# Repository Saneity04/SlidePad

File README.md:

# SlidePad
3x3 matrix with 4 Slider potentiometer running QMK

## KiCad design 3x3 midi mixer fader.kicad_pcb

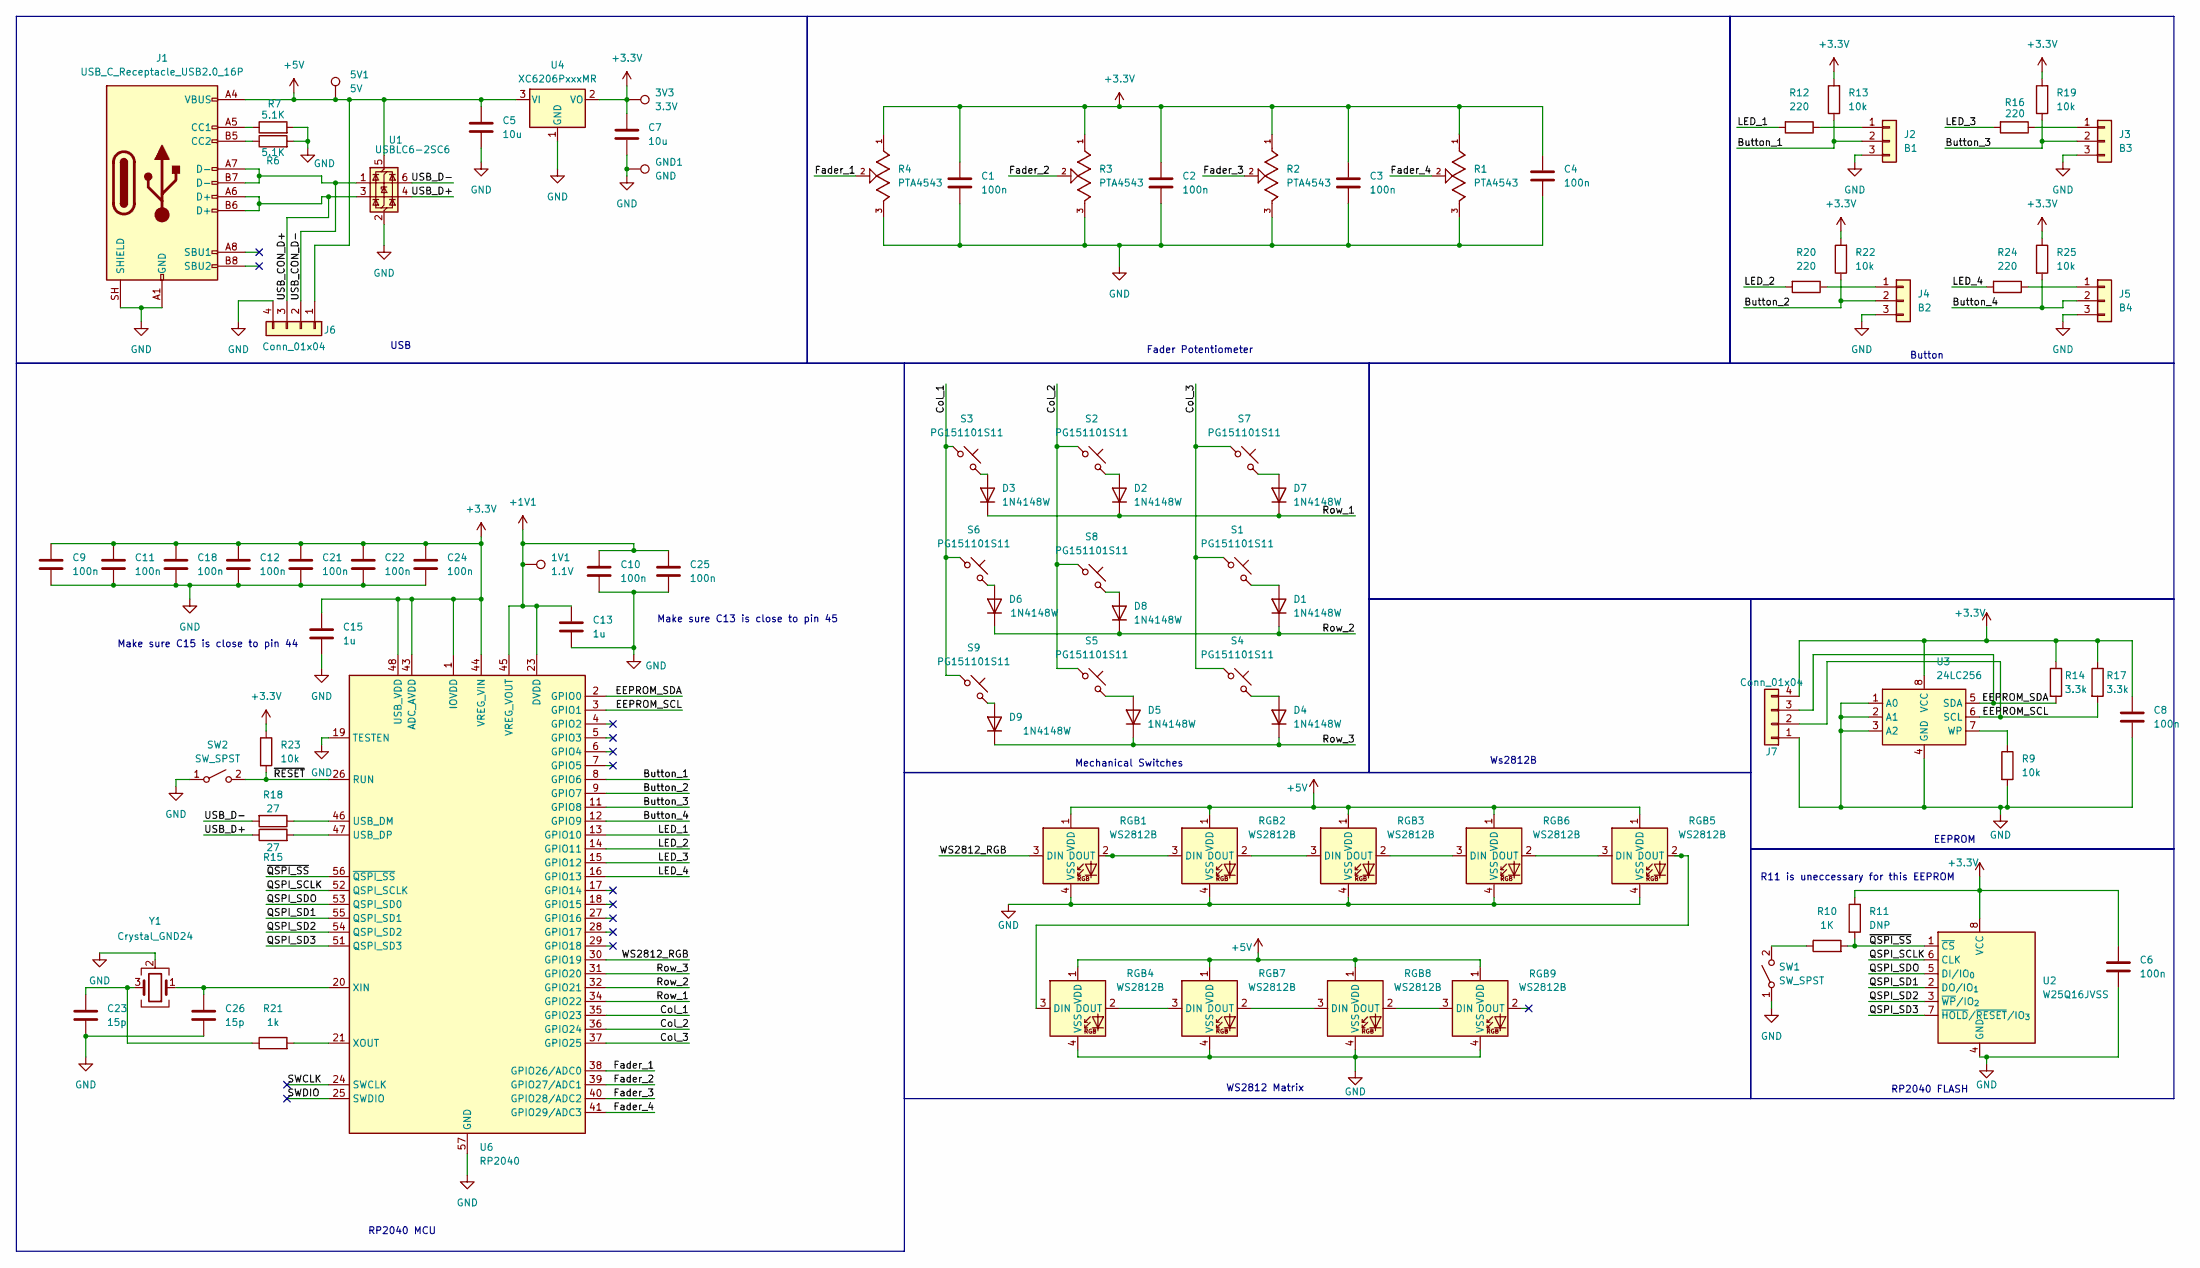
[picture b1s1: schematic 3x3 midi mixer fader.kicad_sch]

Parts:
1V1: 1.1V; TestPoint_Pad_1.5x1.5mm
3V3: 3.3V; TestPoint_Pad_1.5x1.5mm
5V1: 5V; TestPoint_Pad_1.5x1.5mm
C1, C2, C3, C4, C6, C8: 100n; C_0603_1608Metric
C5, C7: 10u; C_0603_1608Metric
C9, C10, C11, C12, C18, C21, C22, C24, C25: 100n; C_0402_1005Metric
C13, C15: 1u; C_0402_1005Metric
C23, C26: 15p; C_0402_1005Metric
D1, D2, D3, D4, D5, D6, D7, D8, D9: 1N4148W; D_SOD-123
GND1: GND; TestPoint_Pad_1.5x1.5mm
J1: USB_C_Receptacle_USB2.0_16P; USB_C_Receptacle_HRO_TYPE-C-31-M-12
J2: B1; JST_XH_B3B-XH-A_1x03_P2.50mm_Vertical
J3: B3; JST_XH_B3B-XH-A_1x03_P2.50mm_Vertical
J4: B2; JST_XH_B3B-XH-A_1x03_P2.50mm_Vertical
J5: B4; JST_XH_B3B-XH-A_1x03_P2.50mm_Vertical
J6: Conn_01x04; JST_XH_B4B-XH-A_1x04_P2.50mm_Vertical
J7: Conn_01x04; PinHeader_1x04_P2.54mm_Vertical
R1, R2, R3, R4: PTA4543; TRIM_PTA4543-2015DPB103; PARTREV 04/21
R6, R7: 5.1K; R_0603_1608Metric
R9, R13, R19, R22, R23, R25: 10k; R_0603_1608Metric
R10: 1K; R_0603_1608Metric
R11: DNP; R_0603_1608Metric
R12, R16, R20, R24: 220; R_0603_1608Metric
R14, R17: 3.3k; R_0603_1608Metric
R15, R18: 27; R_0603_1608Metric
R21: 1k; R_0402_1005Metric
RGB1, RGB2, RGB3, RGB7, RGB8, RGB9: WS2812B; LED_MX_6028R
RGB4, RGB5, RGB6: WS2812B; LED_MX_6028R-ROT
S1, S2, S3, S4, S5, S6, S7, S8, S9: PG151101S11; SW_MX_HS_CPG151101S11_1u; PARTREV A
SW1, SW2: SW_SPST; SW_SPST_SKQG_WithStem
U1: USBLC6-2SC6; SOT-23-6
U2: W25Q16JVSS; SOIC-8_5.3x5.3mm_P1.27mm
U3: 24LC256; SOIC-8_5.3x5.3mm_P1.27mm
U4: XC6206PxxxMR; SOT-23-3
U6: RP2040; QFN-56-1EP_7x7mm_P0.4mm_EP3.2x3.2mm_ThermalVias
Y1: Crystal_GND24; Crystal_SMD_3225-4Pin_3.2x2.5mm

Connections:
+1V1: 1V1.1 (1_1), C10.1, C13.1, C25.1, U6.23 (DVDD), U6.45 (VREG_VOUT), U6.50 (DVDD)
+3.3V: 3V3.1 (1_1), C1.1, C2.1, C3.1, C4.1, C6.1, C7.1, C8.1, C9.1, C11.1, C12.1, C15.1, C18.1, C21.1, C22.1, C24.1, J7.4, R1.1, R2.1, R3.1, R4.1, R11.1, R13.2, R14.1, R17.1, R19.2, R22.2, R23.1, R25.1, U2.8 (VCC), U3.8 (VCC), U4.2 (VO), U6.1 (IOVDD), U6.10 (IOVDD), U6.22 (IOVDD), U6.33 (IOVDD), U6.42 (IOVDD), U6.43 (ADC_AVDD), U6.44 (VREG_VIN), U6.48 (USB_VDD), U6.49 (IOVDD)
+5V: 5V1.1 (1_1), C5.1, J1.A4 (VBUS), J1.A9 (VBUS), J1.B4 (VBUS), J1.B9 (VBUS), J6.1, RGB1.1 (VDD), RGB2.1 (VDD), RGB3.1 (VDD), RGB4.1 (VDD), RGB5.1 (VDD), RGB6.1 (VDD), RGB7.1 (VDD), RGB8.1 (VDD), RGB9.1 (VDD), U1.5 (VBUS), U4.3 (VI)
/Button_1: J2.2, R13.1, U6.8 (GPIO6)
/Button_2: J4.2, R22.1, U6.9 (GPIO7)
/Button_3: J3.2, R19.1, U6.11 (GPIO8)
/Button_4: J5.2, R25.2, U6.12 (GPIO9)
/Col_1: S3.1, S6.1, S9.1, U6.35 (GPIO23)
/Col_2: S2.1, S5.1, S8.1, U6.36 (GPIO24)
/Col_3: S1.1, S4.1, S7.1, U6.37 (GPIO25)
/EEPROM_SCL: J7.2, R17.2, U3.6 (SCL), U6.3 (GPIO1)
/EEPROM_SDA: J7.3, R14.2, U3.5 (SDA), U6.2 (GPIO0)
/Fader_1: R4.2, U6.38 (GPIO26/ADC0)
/Fader_2: R3.2, U6.39 (GPIO27/ADC1)
/Fader_3: R2.2, U6.40 (GPIO28/ADC2)
/Fader_4: R1.2, U6.41 (GPIO29/ADC3)
/LED_1: R12.2, U6.13 (GPIO10)
/LED_2: R20.2, U6.14 (GPIO11)
/LED_3: R16.2, U6.15 (GPIO12)
/LED_4: R24.2, U6.16 (GPIO13)
/QSPI_SCLK: U2.6 (CLK), U6.52 (QSPI_SCLK)
/QSPI_SD1: U2.2 (DO/IO_{1}), U6.55 (QSPI_SD1)
/QSPI_SD2: U2.3 (~WP/IO_{2}), U6.54 (QSPI_SD2)
/QSPI_SD3: U2.7 (~HOLD/~RESET/IO_{3}), U6.51 (QSPI_SD3)
/QSPI_SDO: U2.5 (DI/IO_{0}), U6.53 (QSPI_SD0)
/Row_1: D2.1 (K), D3.1 (K), D7.1 (K), U6.34 (GPIO22)
/Row_2: D1.1 (K), D6.1 (K), D8.1 (K), U6.32 (GPIO21)
/Row_3: D4.1 (K), D5.1 (K), D9.1 (K), U6.31 (GPIO20)
/SWCLK: U6.24 (SWCLK)
/SWDIO: U6.25 (SWDIO)
/USB_CON_D+: J1.A6 (D+), J1.B6 (D+), J6.3, U1.3 (I/O2)
/USB_CON_D-: J1.A7 (D-), J1.B7 (D-), J6.2, U1.1 (I/O1)
/USB_D+: R15.1, U1.4 (I/O2)
/USB_D-: R18.2, U1.6 (I/O1)
/WS2812_RGB: RGB1.3 (DIN), U6.30 (GPIO19)
/~QSPI_SS: R10.2, R11.2, U2.1 (~CS), U6.56 (~QSPI_SS)
/~RESET: R23.2, SW2.2 (B), U6.26 (RUN)
GND: C1.2, C2.2, C3.2, C4.2, C5.2, C6.2, C7.2, C8.2, C9.2, C10.2, C11.2, C12.2, C13.2, C15.2, C18.2, C21.2, C22.2, C23.2, C24.2, C25.2, C26.2, GND1.1 (1_1), J1.A1 (GND), J1.A12 (GND), J1.B1 (GND), J1.B12 (GND), J1.SH (SHIELD), J2.3, J3.3, J4.3, J5.3, J6.4, J7.1, R1.3, R2.3, R3.3, R4.3, R6.2, R7.2, R9.2, RGB1.4 (VSS), RGB2.4 (VSS), RGB3.4 (VSS), RGB4.4 (VSS), RGB5.4 (VSS), RGB6.4 (VSS), RGB7.4 (VSS), RGB8.4 (VSS), RGB9.4 (VSS), SW1.1 (A), SW2.1 (A), U1.2 (GND), U2.4 (GND), U3.1 (A0), U3.2 (A1), U3.3 (A2), U3.4 (GND), U4.1 (GND), U6.19 (TESTEN), U6.57 (GND), Y1.2 (G), Y1.4 (G)
unnamed: C23.1, R21.1, Y1.3
unnamed: D1.2 (A), S1.2
unnamed: D2.2 (A), S2.2
unnamed: D3.2 (A), S3.2
unnamed: D4.2 (A), S4.2
unnamed: D5.2 (A), S5.2
unnamed: D6.2 (A), S6.2
unnamed: D7.2 (A), S7.2
unnamed: D8.2 (A), S8.2
unnamed: D9.2 (A), S9.2
unnamed: J1.A5 (CC1), R7.1
unnamed: J1.B5 (CC2), R6.1
unnamed: J2.1, R12.1
unnamed: J3.1, R16.1
unnamed: J4.1, R20.1
unnamed: J5.1, R24.1
unnamed: RGB1.2 (DOUT), RGB2.3 (DIN)
unnamed: RGB2.2 (DOUT), RGB3.3 (DIN)
unnamed: RGB3.2 (DOUT), RGB6.3 (DIN)
unnamed: RGB4.3 (DIN), RGB5.2 (DOUT)
unnamed: RGB4.2 (DOUT), RGB7.3 (DIN)
unnamed: RGB5.3 (DIN), RGB6.2 (DOUT)
unnamed: RGB7.2 (DOUT), RGB8.3 (DIN)
unnamed: RGB8.2 (DOUT), RGB9.3 (DIN)
unnamed: R10.1, SW1.2 (B)
unnamed: R9.1, U3.7 (WP)
unnamed: R18.1, U6.46 (USB_DM)
unnamed: R15.2, U6.47 (USB_DP)
unnamed: C26.1, U6.20 (XIN), Y1.1
unnamed: R21.2, U6.21 (XOUT)

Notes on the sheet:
USB
WS2812 Matrix
R11 is uneccessary for this EEPROM
Fader Potentiometer
Make sure C13 is close to pin 45
RP2040 MCU
Ws2812B
RP2040 FLASH
Button
EEPROM
Mechanical Switches
Make sure C15 is close to pin 44

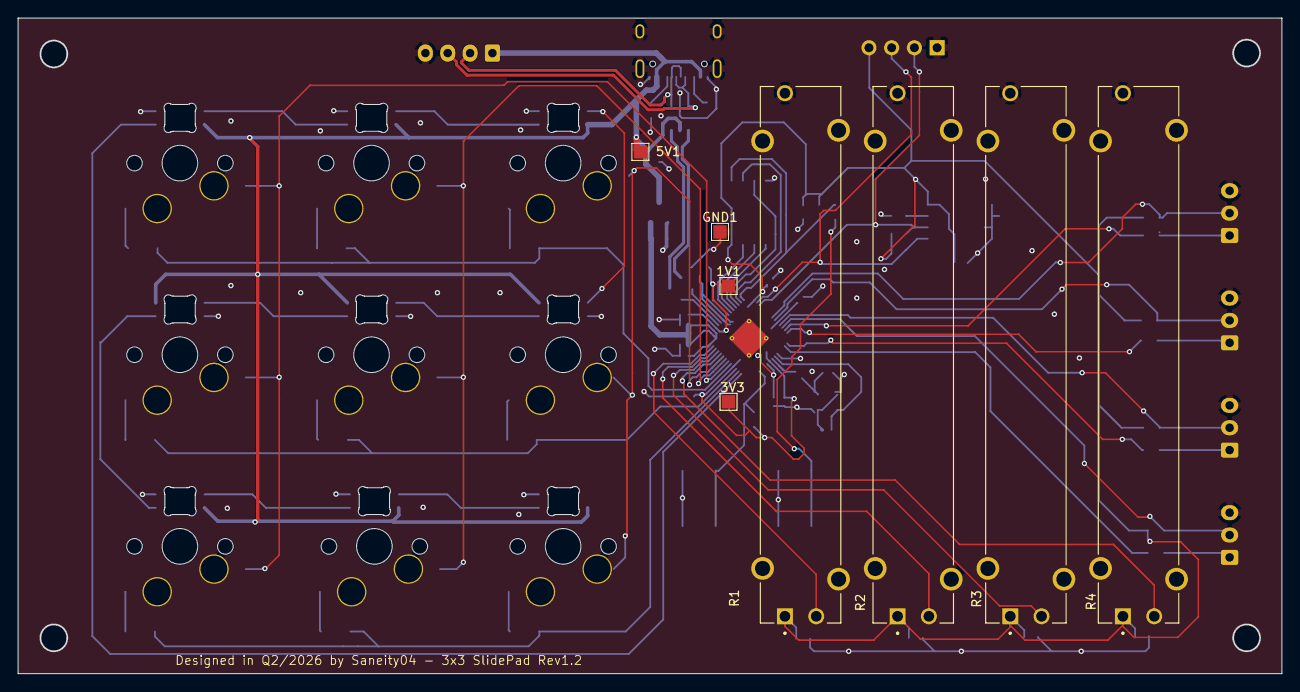
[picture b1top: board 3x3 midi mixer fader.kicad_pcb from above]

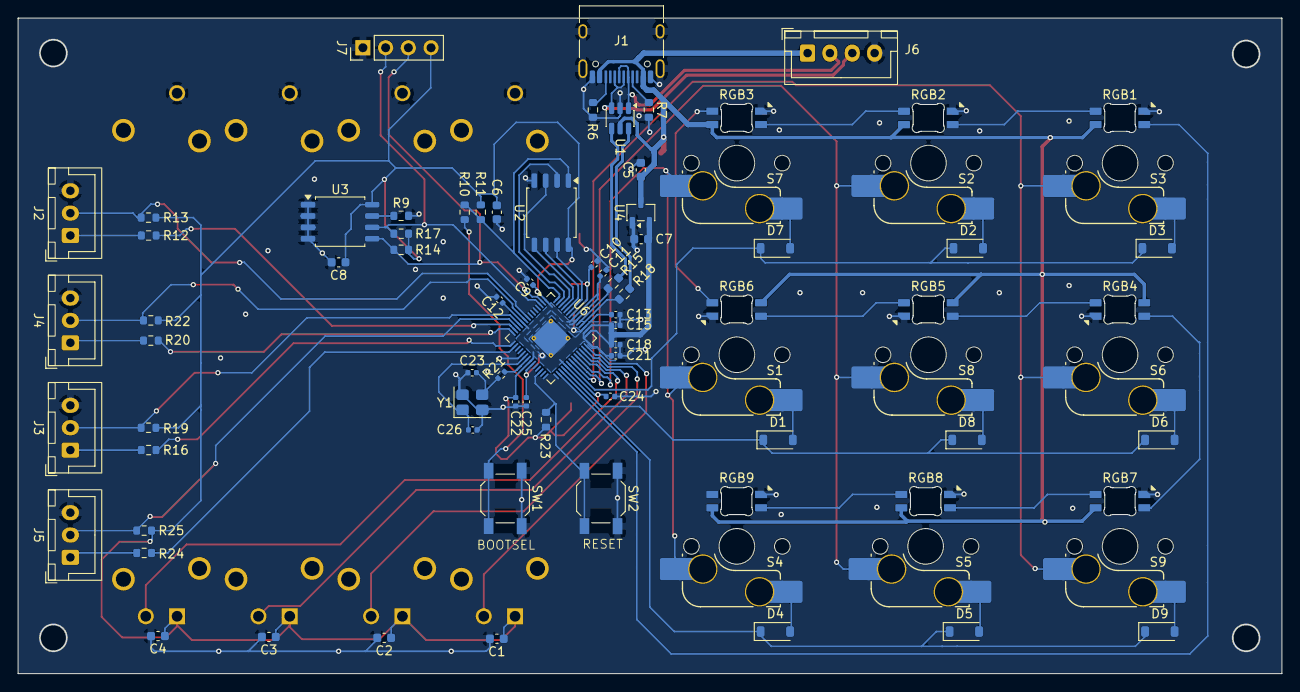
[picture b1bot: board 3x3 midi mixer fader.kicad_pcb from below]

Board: 2 copper layers, 141.2 x 73.2 mm, 90 parts (82 on the bottom side), 66 nets.

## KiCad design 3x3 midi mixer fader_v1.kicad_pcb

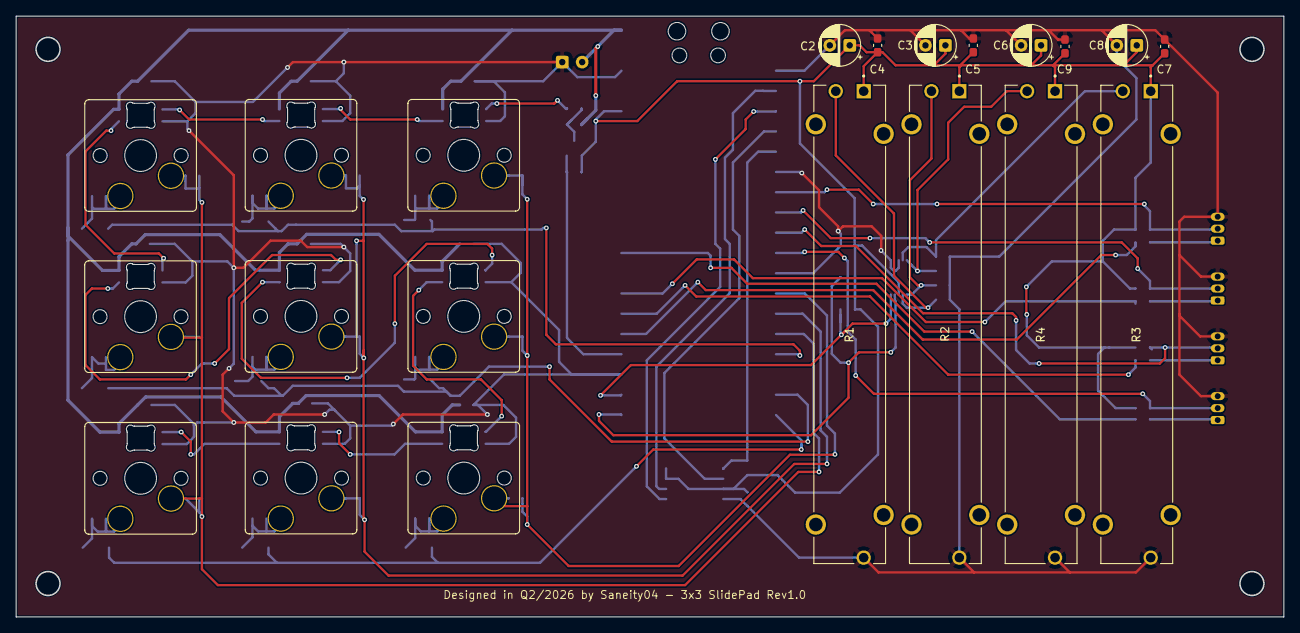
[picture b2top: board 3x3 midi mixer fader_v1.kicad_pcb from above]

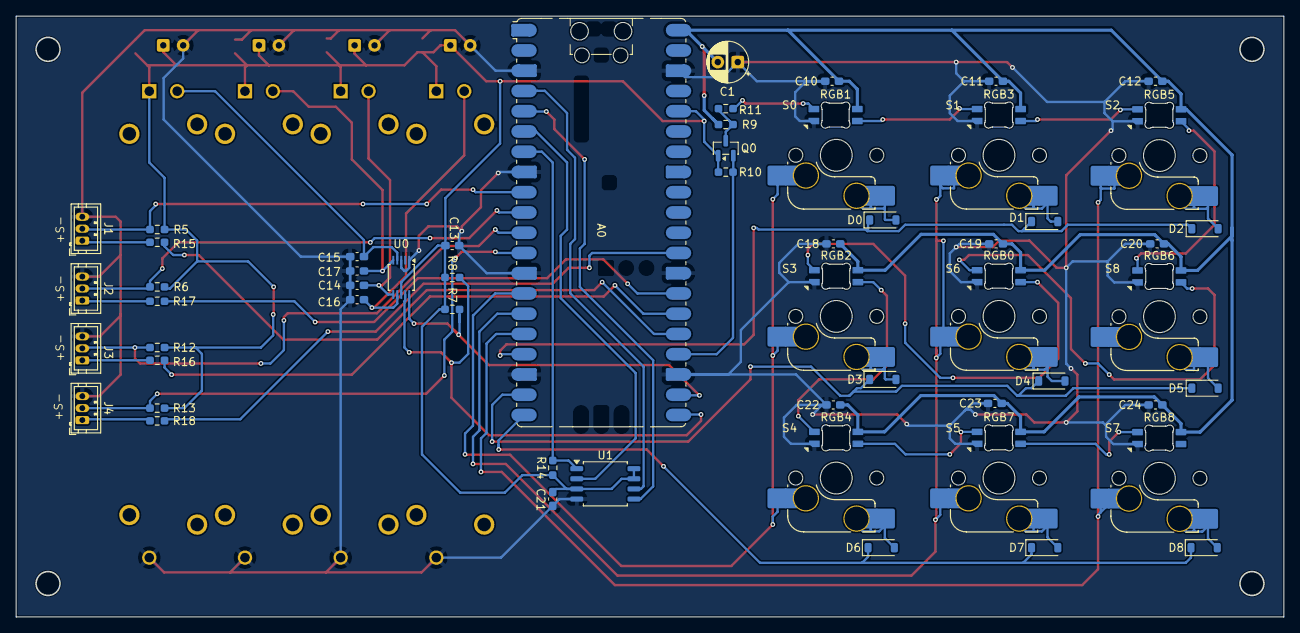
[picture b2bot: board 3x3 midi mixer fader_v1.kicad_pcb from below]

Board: 2 copper layers, 158.9 x 75.2 mm, 77 parts (65 on the bottom side), 51 nets.

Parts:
A0: RaspberryPi_Pico; RaspberryPi_Pico_Common_SMD_No_Antenna
C1: 100uF; CP_Radial_D5.0mm_P2.50mm
C2, C3, C6, C8: 10uF; CP_Radial_D5.0mm_P2.50mm
C4, C5, C7, C9, C10, C11, C12, C13, C14, C15, C16, C17, C18, C19, C20, C21, C22, C23, C24: 0.1uF; C_0603_1608Metric_Pad1.08x0.95mm_HandSolder
D0, D1, D2, D3, D4, D5, D6, D7, D8: 1N4148W; D_SOD-123
J1: B1; JST_ZH_B3B-ZR_1x03_P1.50mm_Vertical
J2: B2; JST_ZH_B3B-ZR_1x03_P1.50mm_Vertical
J3: B3; JST_ZH_B3B-ZR_1x03_P1.50mm_Vertical
J4: B4; JST_ZH_B3B-ZR_1x03_P1.50mm_Vertical
Q0: BSS138; SOT-23
R1, R2, R3, R4: PTA4543; TRIM_PTA4543-2015DPB103
R5, R6, R9, R10, R12, R13, R14: 10k; R_0603_1608Metric_Pad0.98x0.95mm_HandSolder
R7, R8: 4.7k; R_0603_1608Metric_Pad0.98x0.95mm_HandSolder
R11, R15, R16, R17, R18: 220; R_0603_1608Metric_Pad0.98x0.95mm_HandSolder
RGB0, RGB1, RGB2, RGB3, RGB4, RGB5, RGB6, RGB7, RGB8: WS2812B; LED_MX_6028R-ROT
S0, S1, S2, S3, S4, S5, S6, S7, S8: PG151101S11; SW_MX_HS_CPG151101S11_1u
U0: ADS1115IDGS; TSSOP-10_3x3mm_P0.5mm
U1: W25Q128JVS; SOIC-8_5.3x5.3mm_P1.27mm

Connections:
+3.3V: A0.36 (3V3), C2.1, C3.1, C4.1, C5.1, C6.1, C7.1, C8.1, C9.1, C13.1, C21.1, Q0.1 (G), R1.1, R2.1, R3.1, R4.1, R5.1, R6.1, R7.1, R8.1, R10.1, R12.1, R13.1, R14.1, U0.8 (VDD), U1.3 (~WP/IO_{2}), U1.7 (~HOLD/~RESET/IO_{3}), U1.8 (VCC)
+5V: A0.40 (VBUS), C1.2, C10.1, C11.1, C12.1, C18.1, C19.1, C20.1, C22.1, C23.1, C24.1, R9.1, RGB0.1 (VDD), RGB1.1 (VDD), RGB2.1 (VDD), RGB3.1 (VDD), RGB4.1 (VDD), RGB5.1 (VDD), RGB6.1 (VDD), RGB7.1 (VDD), RGB8.1 (VDD)
B1: A0.9 (GPIO6), J1.2, R5.2
B2: A0.10 (GPIO7), J2.2, R6.2
B3: A0.11 (GPIO8), J3.2, R12.2
B4: A0.12 (GPIO9), J4.2, R13.2
Column 1: A0.14 (GPIO10), S0.1, S3.1, S4.1
Column 2: A0.15 (GPIO11), S1.1, S5.1, S6.1
Column 3: A0.16 (GPIO12), S2.1, S7.1, S8.1
Fader 1: C15.1, R3.2, U0.4 (AIN0)
Fader 2: C17.1, R4.2, U0.5 (AIN1)
Fader 3: C14.1, R2.2, U0.6 (AIN2)
Fader 4: C16.1, R1.2, U0.7 (AIN3)
GND: A0.3 (GND), A0.8 (GND), A0.13 (GND), A0.18 (GND), A0.23 (GND), A0.28 (GND), A0.38 (GND), C1.1, C2.2, C3.2, C4.2, C5.2, C6.2, C7.2, C8.2, C9.2, C10.2, C11.2, C12.2, C13.2, C14.2, C15.2, C16.2, C17.2, C18.2, C19.2, C20.2, C21.2, C22.2, C23.2, C24.2, J1.3, J2.3, J3.3, J4.3, R1.3, R2.3, R3.3, R4.3, RGB0.4 (VSS), RGB1.4 (VSS), RGB2.4 (VSS), RGB3.4 (VSS), RGB4.4 (VSS), RGB5.4 (VSS), RGB6.4 (VSS), RGB7.4 (VSS), RGB8.4 (VSS), U0.1 (ADDR), U0.3 (GND), U1.4 (GND)
LED1: A0.25 (GPIO19), R15.2
LED2: A0.26 (GPIO20), R16.2
LED3: A0.27 (GPIO21), R17.2
LED4: A0.29 (GPIO22), R18.2
unnamed: D0.2 (A), S0.2
unnamed: D1.2 (A), S1.2
unnamed: D2.2 (A), S2.2
unnamed: D3.2 (A), S3.2
unnamed: D4.2 (A), S6.2
unnamed: D5.2 (A), S8.2
unnamed: D6.2 (A), S4.2
unnamed: D7.2 (A), S5.2
unnamed: D8.2 (A), S7.2
unnamed: J1.1, R15.1
unnamed: J2.1, R17.1
unnamed: J3.1, R16.1
unnamed: J4.1, R18.1
unnamed: RGB0.3 (DIN), RGB6.2 (DOUT)
unnamed: RGB0.2 (DOUT), RGB2.3 (DIN)
unnamed: R11.1, RGB1.3 (DIN)
unnamed: RGB1.2 (DOUT), RGB3.3 (DIN)
unnamed: RGB2.2 (DOUT), RGB4.3 (DIN)
unnamed: RGB3.2 (DOUT), RGB5.3 (DIN)
unnamed: RGB4.2 (DOUT), RGB7.3 (DIN)
unnamed: RGB5.2 (DOUT), RGB6.3 (DIN)
unnamed: RGB7.2 (DOUT), RGB8.3 (DIN)
Row 1: A0.17 (GPIO13), D0.1 (K), D1.1 (K), D2.1 (K)
Row 2: A0.19 (GPIO14), D3.1 (K), D4.1 (K), D5.1 (K)
Row 3: A0.20 (GPIO15), D6.1 (K), D7.1 (K), D8.1 (K)
SCL: A0.22 (GPIO17), R7.2, U0.10 (SCL)
SDA: A0.21 (GPIO16), R8.2, U0.9 (SDA)
SPI_CLK: A0.4 (GPIO2), U1.6 (CLK)
SPI_CS: A0.7 (GPIO5), R14.2, U1.1 (~CS)
SPI_MISO: A0.6 (GPIO4), U1.2 (DO/IO_{1})
SPI_MOSI: A0.5 (GPIO3), U1.5 (DI/IO_{0})
WS2812IN_HV: Q0.3 (D), R9.2, R11.2
WS2812IN_LV: A0.24 (GPIO18), Q0.2 (S), R10.2

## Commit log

2026-06-04 First Revision QMK/VIAL firmware
